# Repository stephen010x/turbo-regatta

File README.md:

# Turbo Regatta - Pier Pressure

<image src="media/ui-circuit-diagram.png" width="256"></image>
<image src="media/race.jpg" width="256"></image> \
<image src="media/motor.jpg" width="256"></image>
<image src="media/pcb.webp" width="256"></image>

The Turbo Regatta is a collaborative project for engineers at Utah Tech University, which involves designing and building a custom built electric motor, and user interface dashboard, attached to a repurposed pedal boat to be used in the Turbo Regatta Boat Race during the [2025 Utah Tech Engineering Design Day Event](https://mech.utahtech.edu/discovery-design-day/)

As the Computer Engineer of our group named *Pier Pressure*, I was responsible for designing the user interface, the circuit schematics, and programming the two microcontrollers used for this project.

<video controls>
    <source src="media/pier-pressure-intro.mp4" type="video/mp4">
</video>

## Voltage Mapper Circuit

The Voltage Mapper Circuit was used to remap the voltage range 15-18V to 0-5V in order to accurately and safely measure the battery voltage from an Arduino microcontroller.

<image src="media/schematic.webp" width="256"></image>
<image src="media/pcb.webp" width="256"></image> \
<image src="media/model1.webp" width="256"></image>
<image src="media/model2.webp" width="256"></image>

[More about the Voltage Mapper Circuit](voltage-mapper)

## User System Interface

The User Interface, which was driven by an Arduino Uno, displayed motor ESC temperature and battery voltage to a LCD screen, and each motors' RPM was displayed using two servo driven tachometers mounted on the dash.

<image src="media/ui-circuit-diagram.png"></image> \
<image src="media/ui-flow-diagram.png" width="256"></image>
<image src="media/wiring1.webp" width="256"></image>
<!--image src="media/wiring2.webp" width="256"></image-->

[Link to Arduino Code](src/arduino)

## User Control Interface

There were two electric motors propelling the boat. Each motor was controlled with an ESC motor controller, which were both being controlled using an [MSP430 Microcontroller](https://www.ti.com/microcontrollers-mcus-processors/msp430-microcontrollers/overview.html). The MSP430 utilized PWM signals in order to communicate with the two ESCs that drove the motors.

As per the project requirements, no libraries were to be used when developing the code for the MSP430. Instead, features such as analog sampling, and IO pin reads and writes, all had to be interfaced using MSP430 IO registers.

<image src="media/msp430.png" width="350"></image>

[MSP430G2xx User Guide](https://www.ti.com/lit/ug/slau144k/slau144k.pdf?ts=1737596399224)

[Link to MSP430 Code](src/msp430)

## Media

[View More Media](media.md)

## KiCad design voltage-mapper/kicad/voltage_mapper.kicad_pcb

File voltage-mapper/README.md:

[<<< Back to main README](../)

# Voltage-Mapper Circuit

One challenge to overcome was being able to accurately measure battery voltage, which was a mandatory feature on the User Interface. The boat used two 18V Drill batteries, and the goal was to be able to safely step that voltage from the 15-18V range, down to the 0-5V range, such that it could be accurately and safely measured by the Arduino microcontroller that drove the user interface. As a solution, I opted to using a subtracting Op-Amp in order to linearly remap the range 15-18V to 0-5V. With the 15V being the expected voltage for a drained battery, this circuit allowed for the highest possible resolution for measuring battery voltage within the expected voltage range of the battery.

## Voltage-Mapper Design

The circuit was designed using [KiCad's](https://www.kicad.org/) Circuit Schematic software.

The formula derived for the resistors of a subtracting Op-Amp to map one voltage range to another:

```math
\begin{align*}
R_1&=\text{Reference Resistance} \\
R_2&=R_1\frac{V_{min}}{V_{ref}}\Big(1-\frac{V_{ref}-V_{min}}{V_{max}-V_{min}}\Big) \\
R_3&=R_1\frac{V_{min}}{V_{max}-V_{min}}
\end{align*}
```

<image src="../media/schematic.webp" width="512"></image>

## LTSpice Simulation

LTSpice was used to verify the circuit, as well as test safety considerations and reduce several failure points that could potentially damage the microcontrollers. To protect the Arduino against surges, and in the situation where the input voltage gets powered before the reference voltage, a Zener Diode was added to the circuit to limit the voltage to 4.7 Volts.

#### Circuit Verification

<image src="../media/spice.webp" width="512"></image>

This simulation was experimentally verified with the real circuit using university owned laboratory power supplies. Despite concerns about the errors of the chosen resistors, the circuit managed to accurately replicate what is seen in the sim within acceptable margins of error.

#### Circuit Surge Tests

These simulations were to verify that the circuit could handle any combination of reference and input voltages

<image src="../media/graph-safety.webp" width="512"></image>

These predictions were experimentally verified with the real circuit using university owned laboratory power supplies. Through testing, the circuit proved to handle sustained voltages of at least 30V for both the reference and input voltage, which is far more than the batteries are ever expected to output. Through this testing, circuit never exceeded the 4.7 output voltage threshold

## PCB Design

For this circuit, I drafted up a PCB design using [KiCad's](https://www.kicad.org/) PCB Editor, and generated [gerber files](kicad/gerber) that were ready to be sent out to PCB manufacturers.

<image src="../media/pcb.webp" width="512"></image> \
<image src="../media/model1.webp" width="256"></image>
<image src="../media/model2.webp" width="256"></image>

## Final Result

Ultimately, we opted with using a solder board instead of a PCB, as pictured below.

<image src="../media/board.webp" width="256"></image>

This was the circuit that was tested to experiementally verify predictions, and was ultimately the circuit used in our boat to measure battery voltage.

## What Could Have Been Improved

The biggest concern about this circuit was the Op-Amp damaging the Arduino in the situation where the Zener Diode failed or burned up. But as it turns out, the Zener diode ended up being unneccissary. Originally, the Op-Amp was being powered by the input voltage, which typically ranged from 15-18V. However, if the Op-Amp was instead powered by the reference voltage instead, which was a regulated 5V output from the ESCs, then it would successfully and safely limit the output voltage of the Op-Amp to a maximum of 5V, which would have provided a bit more resolution than the maximum of 4.7V that the Zener Diode provided.

Below outlines the LTSpice simulation of the improved circuit, which has not been experimentally verified.

<image src="../media/spice-better.webp" width="512"></image>

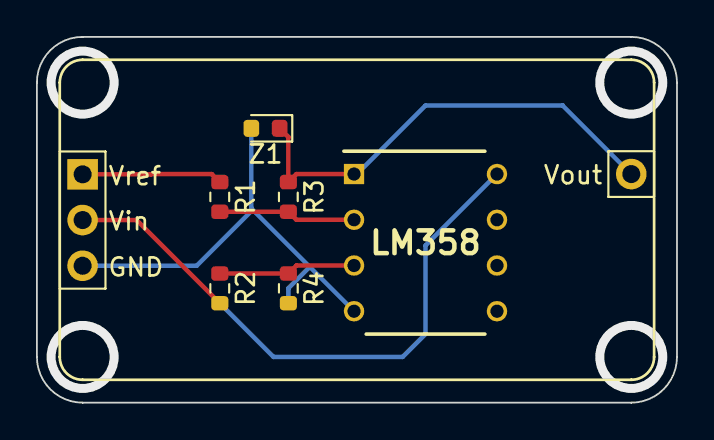
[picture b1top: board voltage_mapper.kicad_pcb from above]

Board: 2 copper layers, 35.6 x 20.3 mm, 8 parts (0 on the bottom side), 6 nets.

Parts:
J1: Conn_01x03_Male; PinHeader_1x03_P2.54mm_Vertical
J2: Conn_01x01_Male; PinHeader_1x01_P2.54mm_Vertical
LM358: LM358APE4; LM358APE4 Footprint
R1: 10kΩ; R_0603_1608Metric
R2: 115kΩ; R_0603_1608Metric
R3, R4: 43kΩ; R_0603_1608Metric
Z1: 1N4732A; D_0603_1608Metric

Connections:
+5V: J1.1, R1.1
+15V: J1.2, LM358.8 (V+), R2.2
/OUT1: J2.1, LM358.1 (OUT1), R3.1, Z1.1 (K)
GND: J1.3, LM358.4 (V-), R4.2, Z1.2 (A)
unnamed: LM358.2 (IN1-), R1.2, R3.2
unnamed: LM358.3 (IN1+), R2.1, R4.1
